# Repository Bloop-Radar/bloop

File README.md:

# Bloop Radar Platform

**Note: Hardware is still under heavy development. Please use at your own risk.**

## What is Bloop?
Bloop is an open-source 24 GHz radar platform aimed to be an easy way for hobbyists, students, and engineers to learn and experiment with radar. 

The goal for this project is not to make an application-specific radar but instead create a flexible platform to learn more about doppler and FMCW radar principles. In order to accomplish this the hardware must be low cost, modular, and allow people to develop their own applications easily. 

Currently, the software solution for Bloop is still unknown as the hardware is still being developed. The plan is to use the ECP5 as the FPGA for this platform and open-source FPGA toolchains available such as [Yosys](https://github.com/YosysHQ/yosys) and [nextpnr](https://github.com/YosysHQ/nextpnr).

## Hardware
The hardware will consist of three modules: an **antenna module** (work in progress), **RF module** ([BGT24 Module](#bgt24-module---rev-a)), and **digital module** (work in progress).

### Planned Hardware Specifications 
* 24 GHz Transceiver MMIC ([BGT24MTR12](https://www.infineon.com/cms/en/product/sensor/radar-image-sensors/radar-sensors/radar-sensors-for-consumer-and-iot/bgt24mtr12/?redirId=117670))
  * 1 TX SMP Connector
  * 2 RX SMP Connectors
* PLL with chirp generation ([LMX2491](http://www.ti.com/product/LMX2491))
* 4 Channel ADC ([ADAR7251](https://www.analog.com/en/products/adar7251.html#))
* ECP5 FPGA
* USB
* ... and more TBD

### BGT24 Module - Rev A

The BGT24 Module is the RF module for the Bloop radar platform, which provides differential I/Q data for RX1 and RX2 along with SPI and modulation control for the LMX2491 PLL and BGT24MTR12 RF transceiver. 

This module will continue to evolve as we test with the SPI Control prototyping hardware and develop some PCB antennas to test with.  

## Prototyping Hardware
Hardware found under `hardware/prototypes` is solely used to develop/evaluate the function of the RF section, BGT24 module, and the ADAR7251 ADC.

### SPI Control - Rev A
Work In Progress under branch `spi_control`  

The SPI Control hardware will include a USB-SPI controller for evaluating the BGT24 Module and ADC. The board will also include an external connector to interface with FPGA development boards.

### RF Front-End - Rev A
The RF Front-End is a panel of various RF microstrip structures to be evaluated for the RF section.

## License
Bloop hardware is distributed under the [Creative Commons Attribution Share Alike 4.0 International](LICENSE.txt)

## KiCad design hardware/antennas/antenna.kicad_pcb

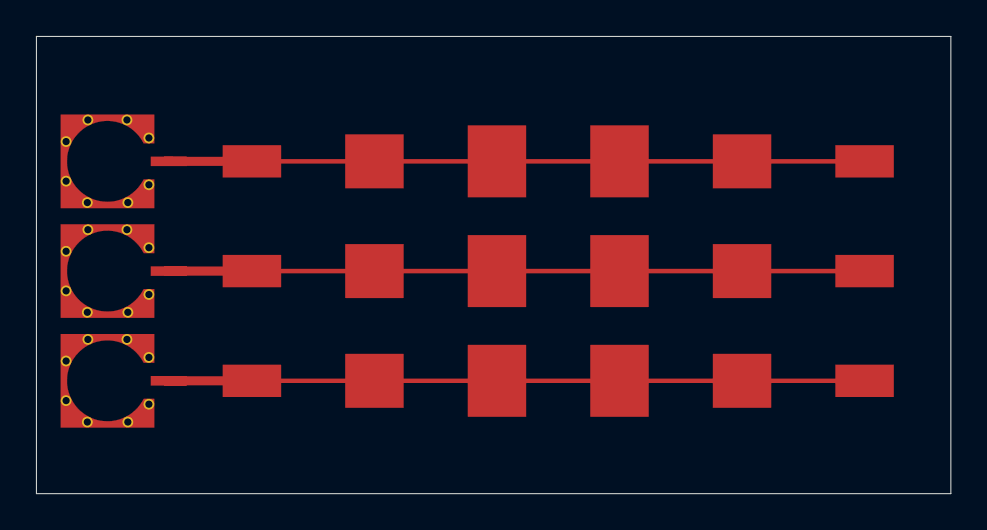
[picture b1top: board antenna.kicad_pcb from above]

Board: 2 copper layers, 50.8 x 25.4 mm, 6 parts (0 on the bottom side), 4 nets, no tracks yet.

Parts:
AE1, AE2, AE3: Antenna; SFPatch_v1
J1, J2, J3: SMP; 85305-0232

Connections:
GNDRF: J1.2, J2.2, J3.2
unnamed: AE1.1, J1.1
unnamed: AE2.1, J2.1
unnamed: AE3.1, J3.1

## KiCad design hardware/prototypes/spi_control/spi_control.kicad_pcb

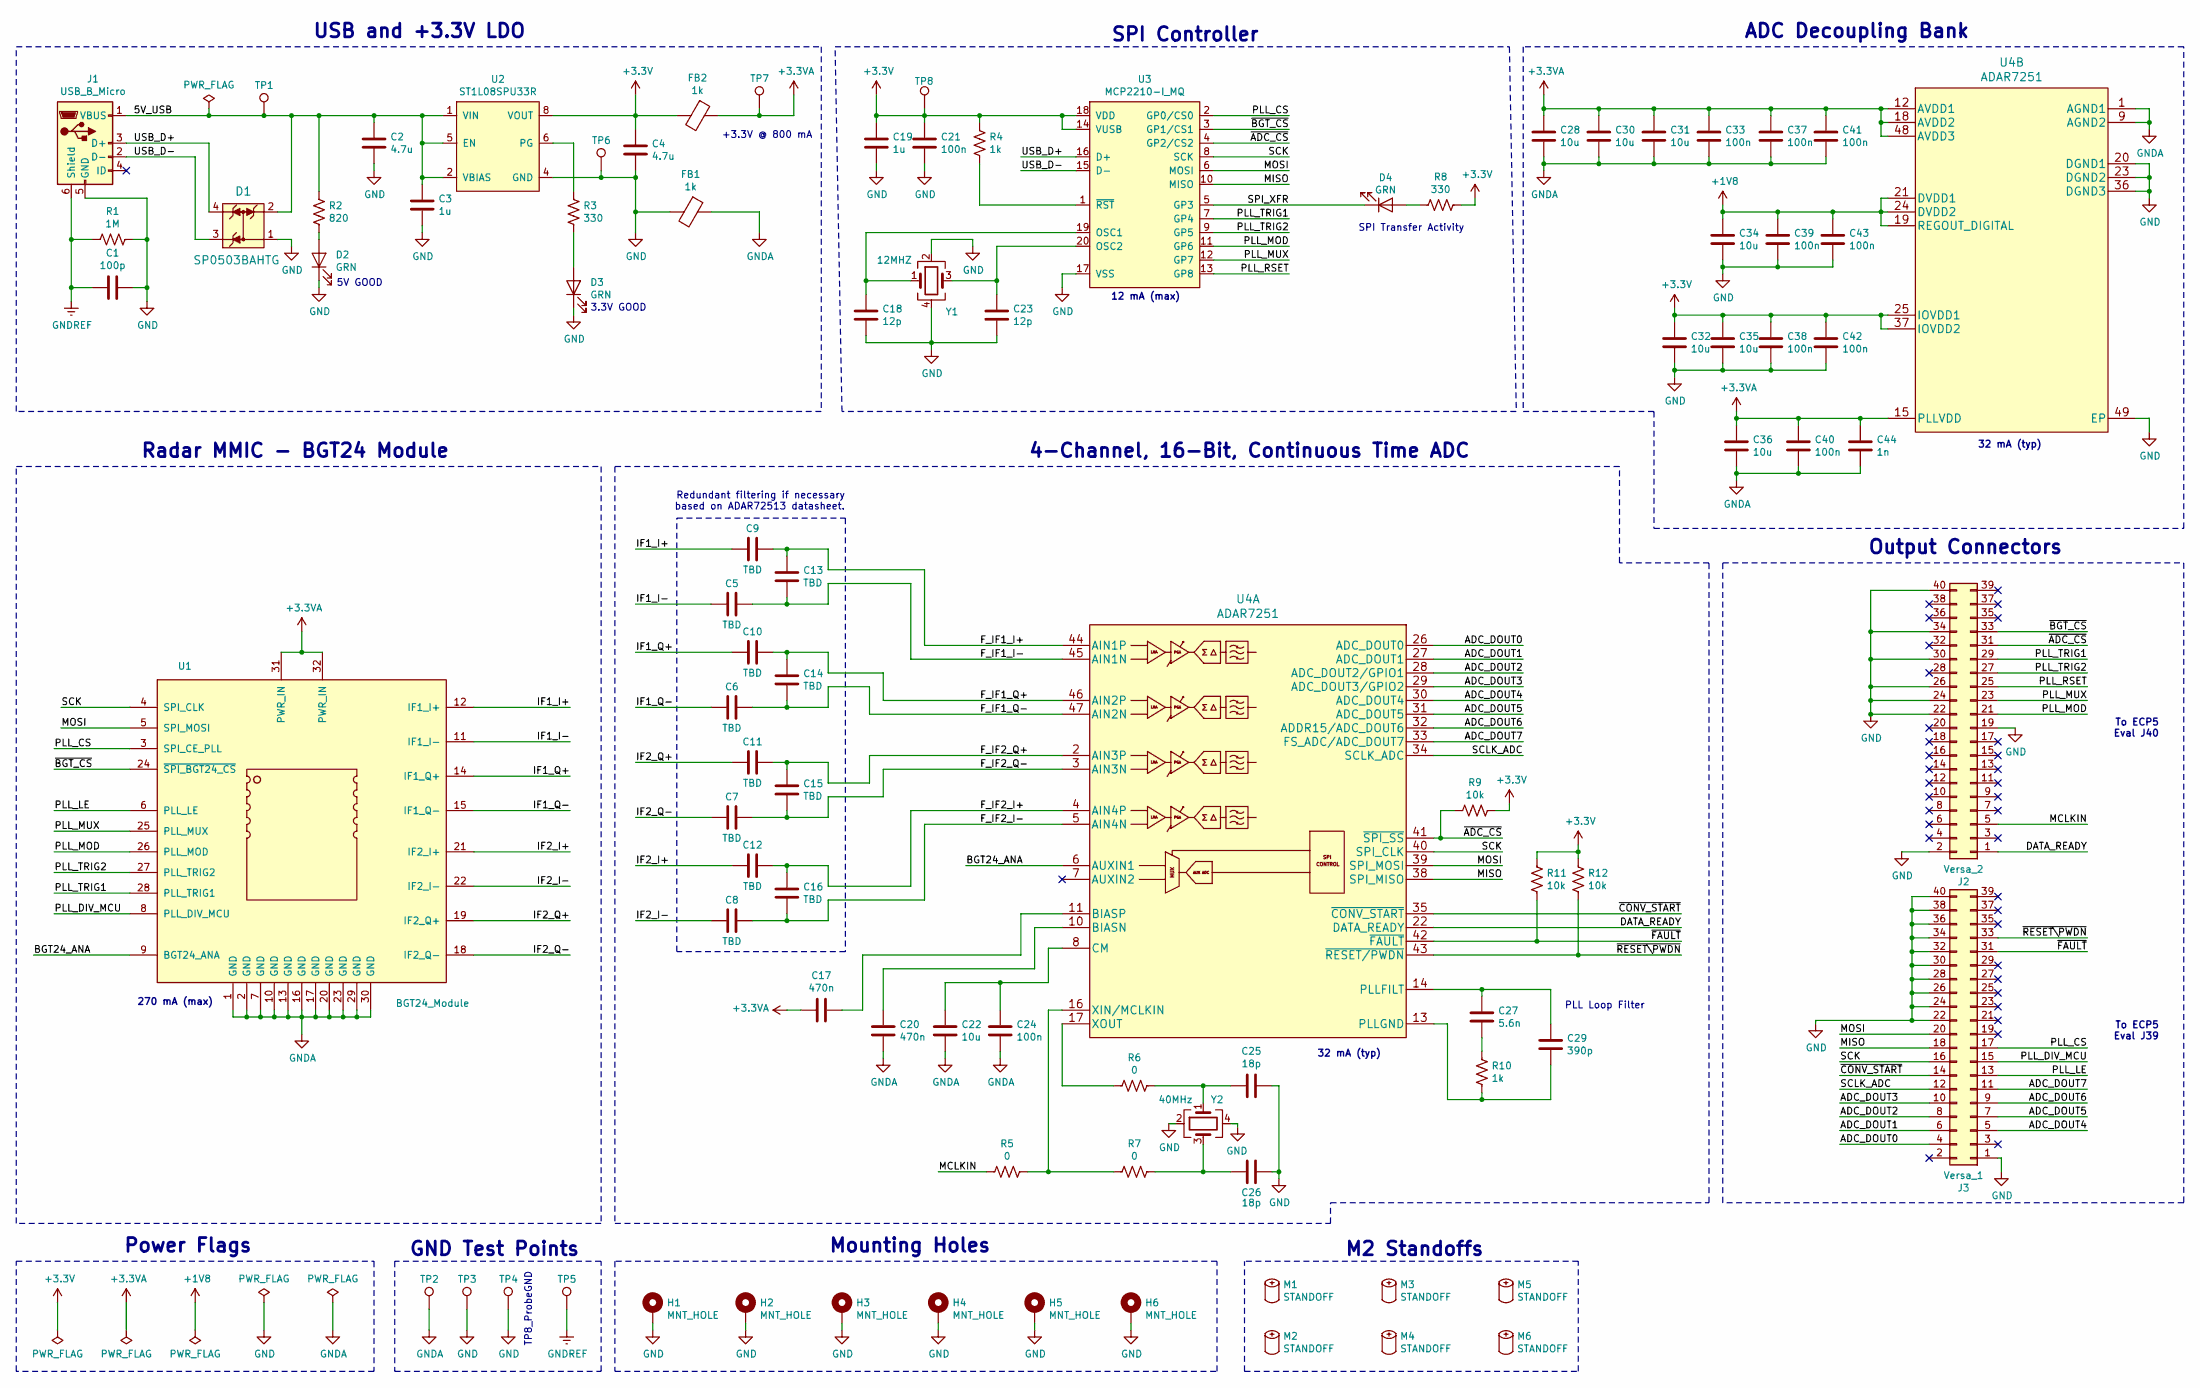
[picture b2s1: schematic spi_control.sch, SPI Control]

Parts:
C1: 100p; C_0402_1005Metric; MPN GCM1555C1H101JA16D; Digi-Key_PN 490-10669-1-ND
C2, C4: 4.7u; C_0402_1005Metric; MPN GRM155R60J475ME47D; Digi-Key_PN 490-5915-1-ND
C3, C19: 1u; C_0402_1005Metric; MPN CL05A105MQ5NNNC; Digi-Key_PN 1276-1235-1-ND
C5, C6, C7, C8, C9, C10, C11, C12, C13, C14, C15, C16: TBD; C_0402_1005Metric
C17, C20: 470n; C_0402_1005Metric; MPN CL05A474KQ5NNNC; Digi-Key_PN 1276-1479-1-ND
C18, C23: 12p; C_0402_1005Metric; MPN C0402C120J5GACTU; Digi-Key_PN 399-1013-1-ND
C21, C24, C33, C37, C38, C39, C40, C41, C42, C43: 100n; C_0402_1005Metric; MPN CL05A104KQ5NNNC; Digi-Key_PN 1276-1442-1-ND
C22, C28, C30, C31, C32, C34, C35, C36: 10u; C_0402_1005Metric; MPN GRM155C80J106ME11D; Digi-Key_PN 490-13233-1-ND
C25, C26: 18p; C_0402_1005Metric; MPN 04025A180JAT2A; Digi-Key_PN 478-1073-1-ND
C27: 5.6n; C_0402_1005Metric; MPN CL05B562KA5NNNC; Digi-Key_PN 1276-1578-1-ND
C29: 390p; C_0402_1005Metric; MPN CL05B391KB5NNNC; Digi-Key_PN 1276-1560-1-ND
C44: 1n; C_0402_1005Metric; MPN C0402C102K5RACTU; Digi-Key_PN 399-1032-1-ND
D1: SP0503BAHTG; SOT-143; MPN SP0503BAHTG; Digi-Key_PN F2715CT-ND
D2, D3, D4: GRN; LED_0402_1005Metric; MPN SML-P13PTT86R; Digi-Key_PN 846-1197-1-ND
FB1, FB2: 1k; L_0603_1608Metric; MPN 742792662; Digi-Key_PN 732-4670-1-ND
H1, H2, H3, H4, H5, H6: MNT_HOLE; MountingHole_2.2mm_M2_Pad_Via
J1: USB_B_Micro; USB_Micro-B_Molex_47346-0001; MPN 10118193-0001LF; Digi-Key_PN 609-4616-1-ND
J2: Versa_2; PinSocket_2x20_P2.54mm_Vertical_SMD; MPN NPTC202KFMS-RC; Digi-Key_PN S5690-ND
J3: Versa_1; PinSocket_2x20_P2.54mm_Vertical_SMD; MPN NPTC202KFMS-RC; Digi-Key_PN S5690-ND
M1, M2, M3, M4, M5, M6: STANDOFF; MPN 970120244; Digi-Key_PN 732-12852-ND
R1: 1M; R_0402_1005Metric; MPN RC0402FR-071ML; Digi-Key_PN 311-1.00MLRCT-ND
R2: 820; R_0402_1005Metric; MPN RC0402JR-07820RL; Digi-Key_PN 311-820JRCT-ND
R3, R8: 330; R_0402_1005Metric; MPN RC0402FR-07330RL; Digi-Key_PN 311-330LRCT-ND
R4, R10: 1k; R_0402_1005Metric; MPN RC0402FR-071KL; Digi-Key_PN 311-1.00KLRCT-ND
R5, R6, R7: 0; R_0402_1005Metric; MPN RC0402JR-070RL; Digi-Key_PN 311-0.0JRCT-ND
R9, R11, R12: 10k; R_0402_1005Metric; MPN RC0402FR-0710KL; Digi-Key_PN 311-10.0KLRCT-ND
TP1, TP2, TP3, TP5, TP6, TP7, TP8: TestPoint; TestPoint_Pad_D1.0mm
TP4: TestPoint; TestPoint_Keystone_5019_Minature; MPN 5019; Digi-Key_PN 36-5019CT-ND
U1: BGT24_Module
U2: ST1L08SPU33R; DFN-8-1EP_2x3mm_P0.5mm_EP0.61x2.2mm; MPN ST1L08SPU33R; Digi-Key_PN 497-15508-1-ND
U3: MCP2210-I_MQ; QFN-20-1EP_5x5mm_P0.65mm_EP3.35x3.35mm; MPN MCP2210-I/MQ; Digi-Key_PN MCP2210-I/MQ-ND
U4: ADAR7251; LFCSP-48-1EP_7x7mm_P0.5mm_EP4.1x4.1mm; MPN ADAR7251WBCSZ; Digi-Key_PN ADAR7251WBCSZ-ND
Y1: 12MHZ; Crystal_SMD_Abracon_ABM8G-4Pin_3.2x2.5mm; MPN ECS-120-12-33-AGN-TR; Digi-Key_PN XC2611CT-ND
Y2: 40MHz; Crystal_SMD_Abracon_ABM8G-4Pin_3.2x2.5mm; MPN ECS-400-18-33-JGN-TR; Digi-Key_PN XC2717CT-ND

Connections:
+1V8: C34.1, C39.1, C43.1, U4.19 (REGOUT_DIGITAL), U4.21 (DVDD1), U4.24 (DVDD2)
+3.3VA: C17.2, C28.1, C30.1, C31.1, C33.1, C36.1, C37.1, C40.1, C41.1, C44.1, FB2.1, TP7.1, U1.31 (PWR_IN), U1.32 (PWR_IN), U4.12 (AVDD1), U4.15 (PLLVDD), U4.18 (AVDD2), U4.48 (AVDD3)
+3V3: C4.1, C19.1, C21.1, C32.1, C35.1, C38.1, C42.1, FB2.2, R4.2, R8.1, R9.1, R11.1, R12.1, TP8.1, U2.8 (VOUT), U3.14 (VUSB), U3.18 (VDD), U4.25 (IOVDD1), U4.37 (IOVDD2)
/5V_USB: C2.1, C3.1, D1.2, J1.1 (VBUS), R2.2, TP1.1, U2.1 (VIN), U2.2 (VBIAS), U2.5 (EN)
/ADC_DOUT0: J3.4, U4.26 (ADC_DOUT0)
/ADC_DOUT1: J3.6, U4.27 (ADC_DOUT1)
/ADC_DOUT2: J3.8, U4.28 (ADC_DOUT2/GPIO1)
/ADC_DOUT3: J3.10, U4.29 (ADC_DOUT3/GPIO2)
/ADC_DOUT4: J3.5, U4.30 (ADC_DOUT4)
/ADC_DOUT5: J3.7, U4.31 (ADC_DOUT5)
/ADC_DOUT6: J3.9, U4.32 (ADDR15/ADC_DOUT6)
/ADC_DOUT7: J3.11, U4.33 (FS_ADC/ADC_DOUT7)
/BGT24_ANA: U1.9 (BGT24_ANA), U4.6 (AUXIN1)
/DATA_READY: J2.1, U4.22 (DATA_READY)
/F_IF1_I+: C9.2, C13.2, U4.44 (AIN1P)
/F_IF1_I-: C5.2, C13.1, U4.45 (AIN1N)
/F_IF1_Q+: C10.2, C14.2, U4.46 (AIN2P)
/F_IF1_Q-: C6.2, C14.1, U4.47 (AIN2N)
/F_IF2_I+: C12.2, C16.2, U4.4 (AIN4P)
/F_IF2_I-: C8.2, C16.1, U4.5 (AIN4N)
/F_IF2_Q+: C11.2, C15.2, U4.2 (AIN3P)
/F_IF2_Q-: C7.2, C15.1, U4.3 (AIN3N)
/IF1_I+: C9.1, U1.12 (IF1_I+)
/IF1_I-: C5.1, U1.11 (IF1_I-)
/IF1_Q+: C10.1, U1.14 (IF1_Q+)
/IF1_Q-: C6.1, U1.15 (IF1_Q-)
/IF2_I+: C12.1, U1.21 (IF2_I+)
/IF2_I-: C8.1, U1.22 (IF2_I-)
/IF2_Q+: C11.1, U1.19 (IF2_Q+)
/IF2_Q-: C7.1, U1.18 (IF2_Q-)
/MCLKIN: J2.5, R5.2
/MISO: J3.18, U3.10 (MISO), U4.38 (SPI_MISO)
/MOSI: J3.20, U1.5 (SPI_MOSI), U3.6 (MOSI), U4.39 (SPI_MOSI)
/PLL_CS: J3.17, U1.3 (SPI_CE_PLL), U3.2 (GP0/CS0)
/PLL_DIV_MCU: J3.15, U1.8 (PLL_DIV_MCU)
/PLL_LE: J3.13, U1.6 (PLL_LE)
/PLL_MOD: J2.21, U1.26 (PLL_MOD), U3.11 (GP6)
/PLL_MUX: J2.23, U1.25 (PLL_MUX), U3.12 (GP7)
/PLL_RSET: J2.25, U3.13 (GP8)
/PLL_TRIG1: J2.29, U1.28 (PLL_TRIG1), U3.7 (GP4)
/PLL_TRIG2: J2.27, U1.27 (PLL_TRIG2), U3.9 (GP5)
/SCK: J3.16, U1.4 (SPI_CLK), U3.8 (SCK), U4.40 (SPI_CLK)
/SCLK_ADC: J3.12, U4.34 (SCLK_ADC)
/SPI_XFR: D4.1 (K), U3.5 (GP3)
/USB_D+: D1.4, J1.3 (D+), U3.16 (D+)
/USB_D-: D1.3, J1.2 (D-), U3.15 (D-)
/~ADC_CS: J2.31, R9.2, U3.4 (GP2/CS2), U4.41 (~SPI_SS)
/~BGT_CS: J2.33, U1.24 (~SPI_BGT24_CS), U3.3 (GP1/CS1)
/~CONV_START: J3.14, U4.35 (~CONV_START)
/~FAULT: J3.31, R11.2, U4.42 (~FAULT)
/~RESET\PWDN: J3.33, R12.2, U4.43 (~RESET/PWDN)
GND: C1.2, C2.2, C3.2, C4.2, C18.1, C19.2, C21.2, C23.1, C25.1, C26.1, C32.2, C34.2, C35.2, C38.2, C39.2, C42.2, C43.2, D1.1, D2.1 (K), D3.1 (K), FB1.2, H1.1, H2.1, H3.1, H4.1, H5.1, H6.1, J1.5 (GND), J2.2, J2.19, J2.22, J2.24, J2.26, J2.30, J2.34, J2.40, J3.1, J3.22, J3.24, J3.26, J3.28, J3.30, J3.32, J3.34, J3.36, J3.38, J3.40, R1.2, TP3.1, TP4.1, TP6.1, U2.4 (GND), U3.17 (VSS), U4.20 (DGND1), U4.23 (DGND2), U4.36 (DGND3), U4.49 (EP), Y1.2, Y1.4, Y2.2, Y2.4
GNDA: C20.2, C22.2, C24.2, C28.2, C30.2, C31.2, C33.2, C36.2, C37.2, C40.2, C41.2, C44.2, FB1.1, TP2.1, U1.1 (GND), U1.2 (GND), U1.7 (GND), U1.10 (GND), U1.13 (GND), U1.16 (GND), U1.17 (GND), U1.20 (GND), U1.23 (GND), U1.29 (GND), U1.30 (GND), U4.1 (AGND1), U4.9 (AGND2)
GNDREF: C1.1, J1.6 (Shield), R1.1, TP5.1
unnamed: C17.1, U4.11 (BIASP)
unnamed: C18.2, U3.19 (OSC1), Y1.1
unnamed: C20.1, U4.10 (BIASN)
unnamed: C22.1, C24.1, U4.8 (CM)
unnamed: C23.2, U3.20 (OSC2), Y1.3
unnamed: C25.2, R6.1, Y2.1
unnamed: C26.2, R7.1, Y2.3
unnamed: C27.1, C29.1, U4.14 (PLLFILT)
unnamed: C27.2, R10.1
unnamed: C29.2, R10.2, U4.13 (PLLGND)
unnamed: D2.2 (A), R2.1
unnamed: D3.2 (A), R3.1
unnamed: D4.2 (A), R8.2
unnamed: R3.2, U2.6 (PG)
unnamed: R4.1, U3.1 (~RST)
unnamed: R5.1, R7.2, U4.16 (XIN/MCLKIN)
unnamed: R6.2, U4.17 (XOUT)

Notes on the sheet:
5V GOOD
3.3V GOOD
SPI Controller
USB and +3.3V LDO
PLL Loop Filter
Power Flags
12 mA (max)
ADC Decoupling Bank
Output Connectors
SPI Transfer Activity
4-Channel, 16-Bit, Continuous Time ADC
GND Test Points
Redundant filtering if necessary based on ADAR72513 datasheet.
Radar MMIC - BGT24 Module
TP8_ProbeGND
Mounting Holes
32 mA (typ)
M2 Standoffs
270 mA (max)
+3.3V @ 800 mA
To ECP5 Eval J40
To ECP5 Eval J39

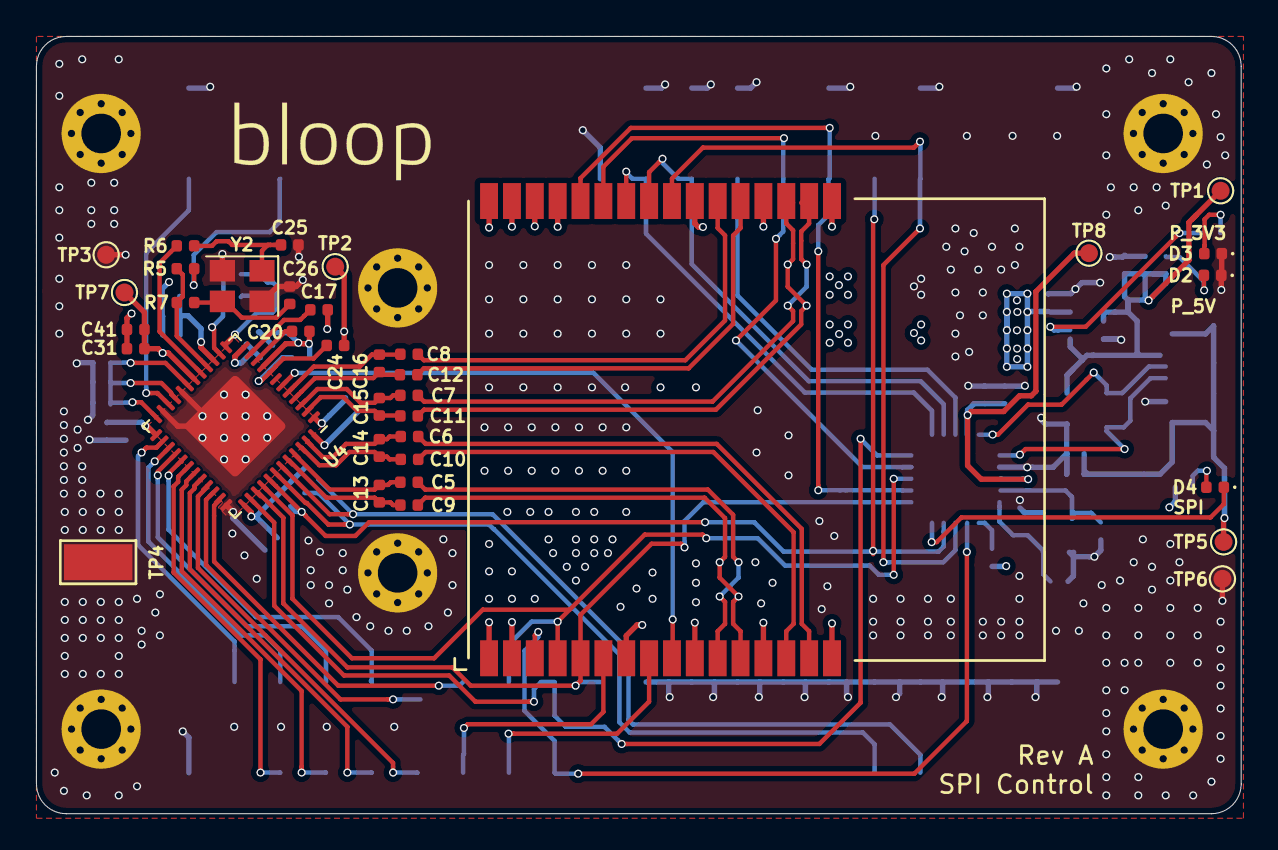
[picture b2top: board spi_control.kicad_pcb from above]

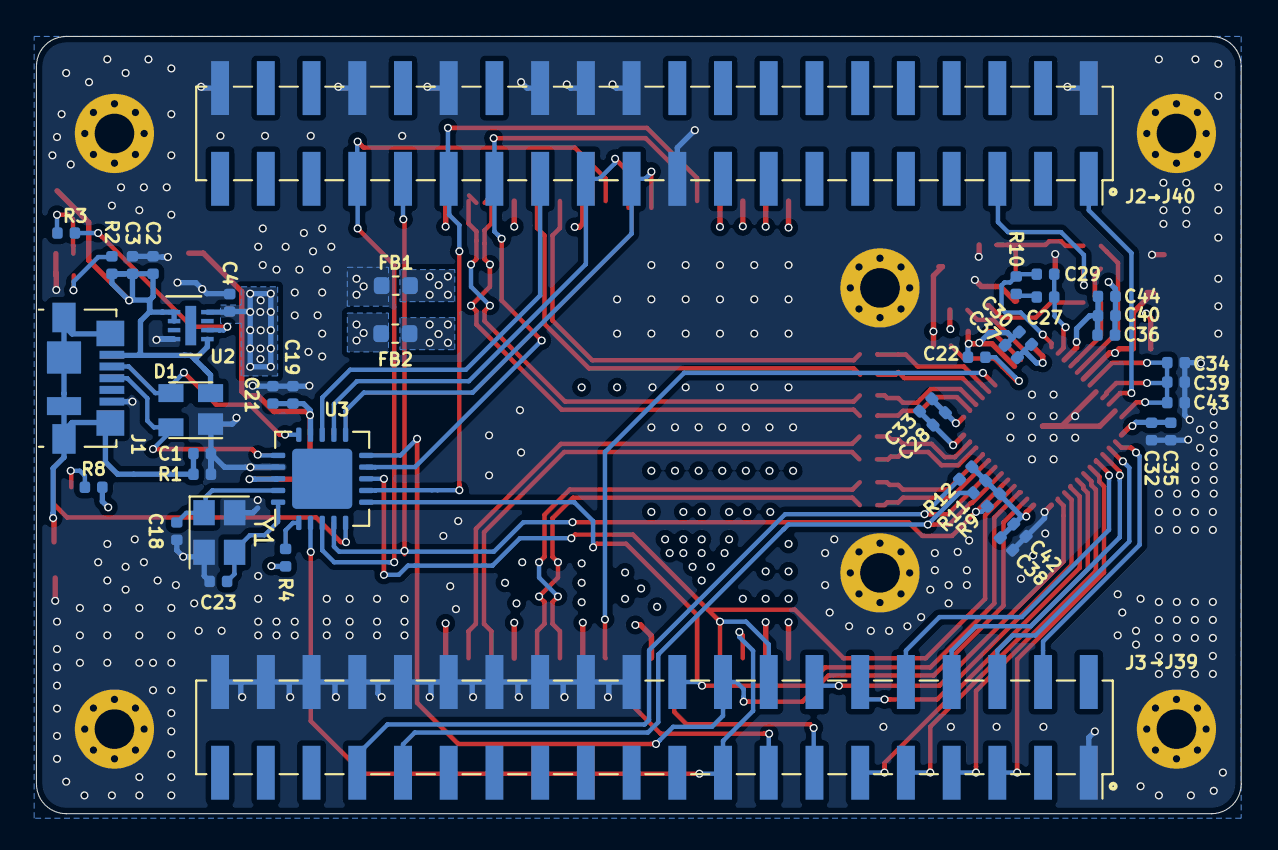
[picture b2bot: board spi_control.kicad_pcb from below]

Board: 4 copper layers, 66.9 x 43.2 mm, 85 parts (43 on the bottom side), 71 nets.

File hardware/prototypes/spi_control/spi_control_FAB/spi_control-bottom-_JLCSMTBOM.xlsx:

Comment | Designator | Footprint | Description
100n | C21, C33, C37, C38, C39, C40, C42, C43 | C_0402_1005Metric | CAP CER 0.1UF 6.3V X5R 0402
1n | C44 | C_0402_1005Metric | CAP CER 1000PF 50V X7R 0402
100p | C1 | C_0402_1005Metric | CAP CER 100PF 50V C0G/NP0 0402
10u | C22, C28, C30, C32, C34, C35, C36 | C_0402_1005Metric | CAP CER 10UF 6.3V X6S 0402
12p | C18, C23 | C_0402_1005Metric | CAP CER 12PF 50V C0G/NP0 0402
1u | C3, C19 | C_0402_1005Metric | CAP CER 1UF 6.3V X5R 0402
390p | C29 | C_0402_1005Metric | CAP CER 390PF 50V X7R 0402
4.7u | C2, C4 | C_0402_1005Metric | CAP CER 4.7UF 6.3V X5R 0402
5.6n | C27 | C_0402_1005Metric | CAP CER 5600PF 25V X7R 0402
10k | R9, R11, R12 | R_0402_1005Metric | RES SMD 10K OHM 1% 1/16W 0402
1k | R4, R10 | R_0402_1005Metric | RES SMD 1K OHM 1% 1/16W 0402
1M | R1 | R_0402_1005Metric | RES SMD 1M OHM 1% 1/16W 0402
330 | R3, R8 | R_0402_1005Metric | RES SMD 330 OHM 1% 1/16W 0402
820 | R2 | R_0402_1005Metric | RES SMD 820 OHM 5% 1/16W 0402
SP0503BAHTG | D1 | SOT-143 | TVS DIODE 5.5V 8.5V SOT143-4
MCP2210-I_MQ | U3 | QFN-20-1EP_5x5mm_P0.65mm_EP3.35x3.35mm | IC CONVERTER USB-SPI 20-QFN
ST1L08SPU33R | U2 | DFN-8-1EP_2x3mm_P0.5mm_EP0.61x2.2mm | IC REG LINEAR 3.3V 800MA 8DFN
12MHZ | Y1 | Crystal_SMD_Abracon_ABM8G-4Pin_3.2x2.5mm | CRYSTAL 12MHZ 12PF SMD
1k | FB1, FB2 | L_0603_1608Metric | FERRITE BEAD 1 KOHM 0603 1LN
Versa_2 | J2 | PinSocket_2x20_P2.54mm_Vertical_SMD | CONN HDR 40POS 0.1 TIN SMD
Versa_1 | J3 | PinSocket_2x20_P2.54mm_Vertical_SMD | CONN HDR 40POS 0.1 TIN SMD
USB_B_Micro | J1 | USB_Micro-B_Molex_47346-0001 | CONN RCPT USB2.0 MICRO B SMD R/A

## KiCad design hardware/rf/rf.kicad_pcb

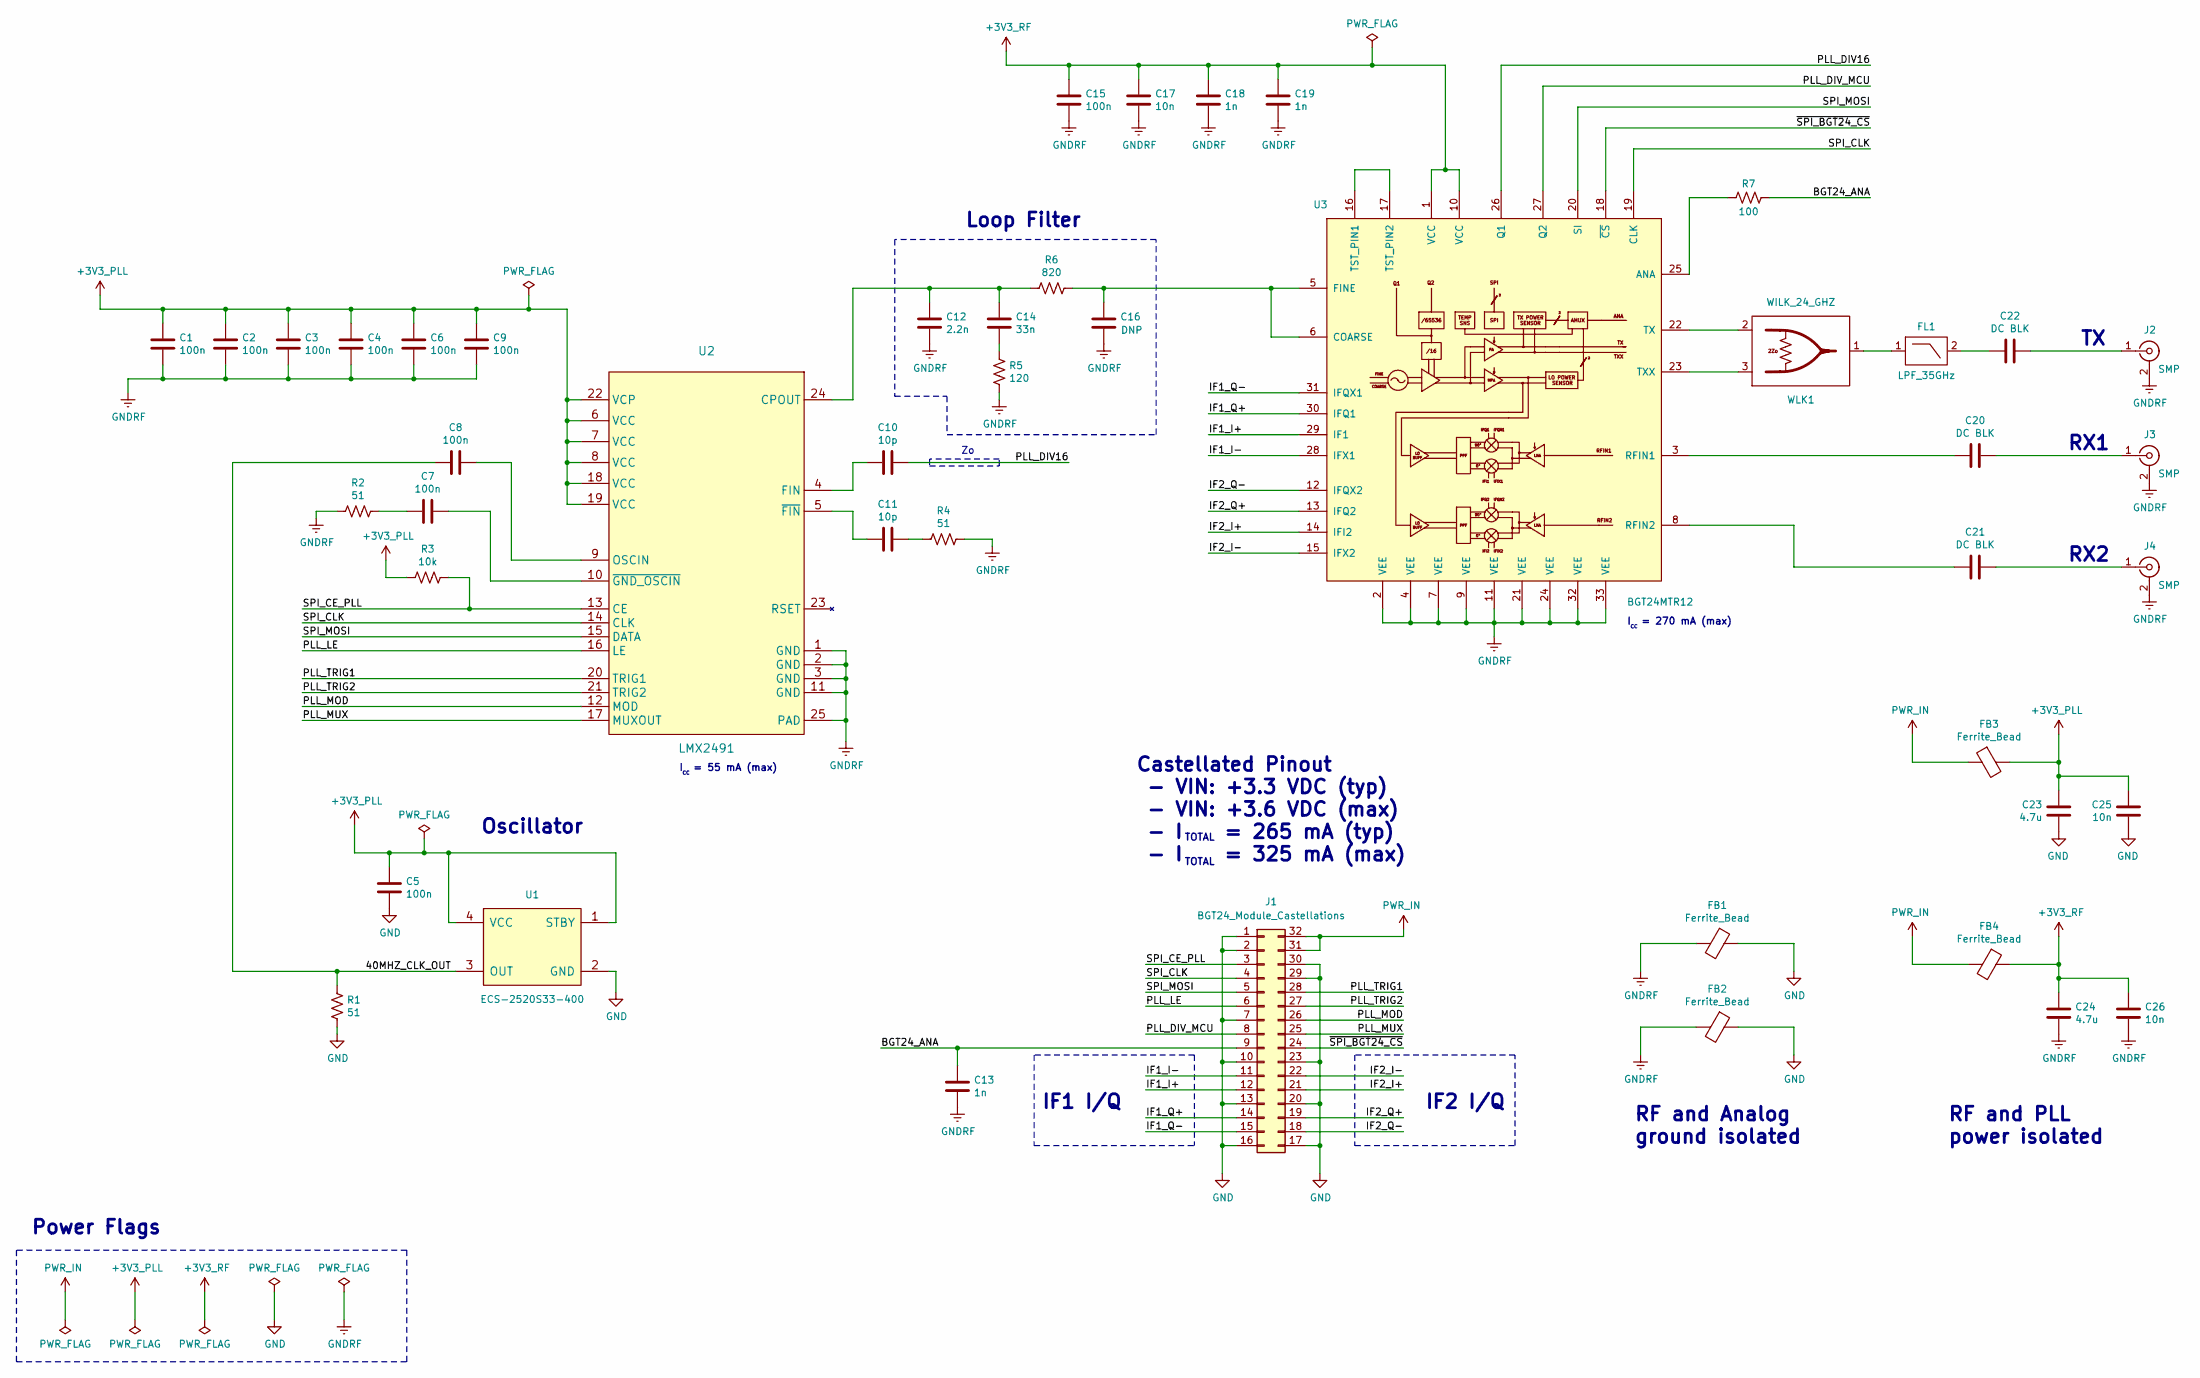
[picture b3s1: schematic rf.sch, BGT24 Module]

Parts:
C1, C2, C3, C4, C5, C6, C7, C8, C9, C15: 100n; C_0201_0603Metric; MPN GRM033R6YA104KE14D
C10, C11: 10p; C_0402_1005Metric; MPN GCM1555C1H100GA16D
C12: 2.2n; C_0201_0603Metric; MPN GRM033R61C223KE84D
C13, C18, C19: 1n; C_0201_0603Metric; MPN GRM033R71H102KA12D
C14: 33n; C_0201_0603Metric; MPN GRM033R61C333KE84D
C16: C_0201_0603Metric
C17, C25, C26: 10n; C_0201_0603Metric; MPN GRM033R71E103KE14D
C20, C21, C22: DC BLK; DC_Block
C23, C24: 4.7u; C_0603_1608Metric; MPN GRM188R61E475KE11D
FB1, FB2, FB3, FB4: Ferrite_Bead; L_0402_1005Metric; MPN MPZ1005S121CT000
FL1: LPF_35GHz; 35GHz_LPF
J1: BGT24_Module_Castellations
J2, J3, J4: SMP; 85305-0232; MPN 0853050232
R1, R2, R4: 51; R_0201_0603Metric; MPN ERJ-1GNF51R0C
R3: 10k; R_0201_0603Metric; MPN ERJ-1GNF1002C
R5: 120; R_0201_0603Metric; MPN ERJ-1GNJ121C
R6: 820; R_0201_0603Metric; MPN ERJ-1GNF8200C
R7: 100; R_0201_0603Metric; MPN ERJ-1GNF1000C
U1: ECS-2520S33-400; Crystal_SMD_2520-4Pin_2.5x2.0mm; MPN ECS-2520S33-400-FN-TR
U2: LMX2491; VQFN-24-1EP_4x4mm_P0.5mm_EP2.45x2.45mm; MPN LMX2491RTWR
U3: BGT24MTR12; MPN BGT24MTR12E6327XUMA1
WLK1: WILK_24_GHZ; Wilk_AWR_Mod

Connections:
+3V3_PLL: C1.1, C2.1, C3.1, C4.1, C5.1, C6.1, C9.1, C23.1, C25.1, FB3.2, R3.2, U1.1 (STBY), U1.4 (VCC), U2.6 (VCC), U2.7 (VCC), U2.8 (VCC), U2.18 (VCC), U2.19 (VCC), U2.22 (VCP)
+3V3_RF: C15.1, C17.1, C18.1, C19.1, C24.1, C26.1, FB4.1, U3.1 (VCC), U3.10 (VCC)
/40MHZ_CLK_OUT: C8.1, R1.1, U1.3 (OUT)
/BGT24_ANA: C13.1, J1.9, R7.1
/IF1_I+: J1.12, U3.29 (IF1)
/IF1_I-: J1.11, U3.28 (IFX1)
/IF1_Q+: J1.14, U3.30 (IFQ1)
/IF1_Q-: J1.15, U3.31 (IFQX1)
/IF2_I+: J1.21, U3.14 (IFI2)
/IF2_I-: J1.22, U3.15 (IFX2)
/IF2_Q+: J1.19, U3.13 (IFQ2)
/IF2_Q-: J1.18, U3.12 (IFQX2)
/PLL_DIV16: C10.1, U3.26 (Q1)
/PLL_DIV_MCU: J1.8, U3.27 (Q2)
/PLL_LE: J1.6, U2.16 (LE)
/PLL_MOD: J1.26, U2.12 (MOD)
/PLL_MUX: J1.25, U2.17 (MUXOUT)
/PLL_TRIG1: J1.28, U2.20 (TRIG1)
/PLL_TRIG2: J1.27, U2.21 (TRIG2)
/SPI_CE_PLL: J1.3, R3.1, U2.13 (CE)
/SPI_CLK: J1.4, U2.14 (CLK), U3.19 (CLK)
/SPI_MOSI: J1.5, U2.15 (DATA), U3.20 (SI)
/~SPI_BGT24_CS: J1.24, U3.18 (~CS)
GND: C5.2, C23.2, C25.2, FB1.1, FB2.1, J1.1, J1.2, J1.7, J1.10, J1.13, J1.16, J1.17, J1.20, J1.23, J1.29, J1.30, R1.2, U1.2 (GND)
GNDRF: C1.2, C2.2, C3.2, C4.2, C6.2, C9.2, C12.2, C13.2, C15.2, C16.2, C17.2, C18.2, C19.2, C24.2, C26.2, FB1.2, FB2.2, J2.2 (Ext), J3.2 (Ext), J4.2 (Ext), R2.2, R4.1, R5.2, U2.1 (GND), U2.2 (GND), U2.3 (GND), U2.11 (GND), U2.25 (PAD), U3.2 (VEE), U3.4 (VEE), U3.7 (VEE), U3.9 (VEE), U3.11 (VEE), U3.21 (VEE), U3.24 (VEE), U3.32 (VEE), U3.33 (VEE)
unnamed: C7.1, R2.1
unnamed: C7.2, U2.10 (~GND_OSCIN)
unnamed: C8.2, U2.9 (OSCIN)
unnamed: C10.2, U2.4 (FIN)
unnamed: C11.1, R4.2
unnamed: C11.2, U2.5 (~FIN)
unnamed: C12.1, C14.1, R6.2, U2.24 (CPOUT)
unnamed: C14.2, R5.1
unnamed: C16.1, R6.1, U3.5 (FINE), U3.6 (COARSE)
unnamed: C20.1, J3.1 (In)
unnamed: C20.2, U3.3 (RFIN1)
unnamed: C21.1, J4.1 (In)
unnamed: C21.2, U3.8 (RFIN2)
unnamed: C22.1, J2.1 (In)
unnamed: C22.2, FL1.2 (OUT)
unnamed: FL1.1 (IN), WLK1.1
unnamed: R7.2, U3.25 (ANA)
unnamed: U3.16 (TST_PIN1), U3.17 (TST_PIN2)
unnamed: U3.22 (TX), WLK1.2
unnamed: U3.23 (TXX), WLK1.3
PWR_IN: FB3.1, FB4.2, J1.31, J1.32

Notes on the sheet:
Loop Filter
Power Flags
Oscillator
I = 270 mA (max)
IF2 I/Q
RF and Analog ground isolated
Castellated Pinout - VIN: +3.3 VDC (typ) - VIN: +3.6 VDC (max) - I = 265 mA (typ) - I = 325 mA (max)
TOTAL
I = 55 mA (max)
RX1
RX2
IF1 I/Q
RF and PLL power isolated

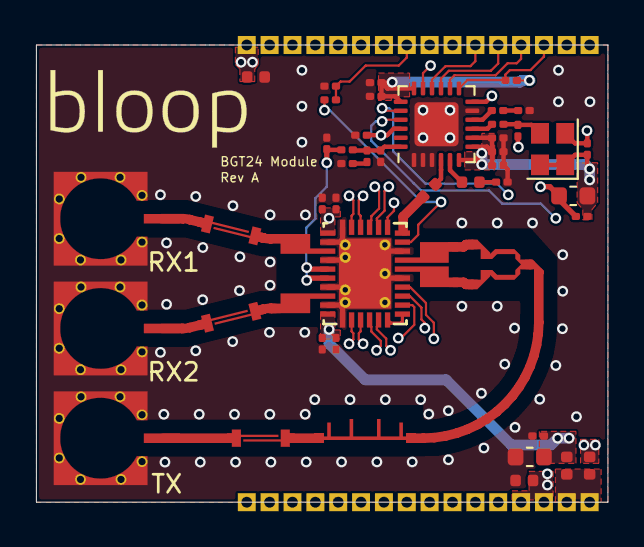
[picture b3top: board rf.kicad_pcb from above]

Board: 4 copper layers, 31.8 x 25.4 mm, 46 parts (1 on the bottom side), 46 nets.

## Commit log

2019-07-27 Initial radar pcb project framework Added 35GHz_LPF footprint
2019-07-27 Created Schematic Worksheet
2019-07-27 Added bloop schematic symbol library Added LPF_35GHz schematic symbol
2019-07-28 Make worksheet template relative-path based
2019-07-28 Added schematic hierarchial sheets
2019-07-28 Radar MMIC symbol; Pcbnew worksheet template added to bloop.kicad_pcb
2019-07-28 Add background color to radar MMIC symbol
2019-07-28 Add wilkinson symbol
2019-07-28 Added 3d SMP footprint and model
2019-07-28 Corrected 3d model path for SMP connector 0734153320
2019-07-28 Added BGT24MTR12 VQFN-32-9 footprint Updated gold material on 3d model 734153320
2019-07-28 Rearrange pins for aesthetic reasons
2019-07-28 Add rev; add titles to schematic sheets
2019-07-28 Move power sheet box
2019-07-28 Make schematic box text size larger
2019-07-28 Started PLL circuitry Added PLL device and oscillator Still need loop filter and clock filter circuits
2019-07-29 Add DC blocking capacitors; add larger resistor and capacitor symbols; implement root PN for symbols
2019-07-30 fixing MPNs
2019-08-06 Add stubs to RX portion; move blocking caps
2019-08-10 Updates to footprint library
2019-08-10 Add edge-launch SWM connector footprint and 3D model
2019-08-10 Preliminary layout
2019-08-11 Layout edits
2019-08-11 Add 100 ohm resistors to wilkinson dividers
2019-08-11 Created Wilk1.mod
2019-08-11 Updates to front end layout
2019-08-16 Remove paste layer from filters; increase mask distance on front_end board
2019-08-19 Corrected transmision line clearance
2019-08-25 Added Infineon Wilkinson
2019-08-25 Corrected Infineon Wilkinson footprint
2019-08-25 Infineon Netclass
2019-08-25 Added infineon wilkinson to layout
2019-08-25 Added Taper 8 24Ghz wilk/matched on PCB
    Added Taper 8 24Ghz wilk/matched on PCB
2019-09-14 Started rough layout for panelization of front end pcbs
2019-09-14 Removed matching stubs from front end schematic
2019-09-15 Preliminary panel for front end pcbs
2019-09-15 Updated panel tab footprint
2019-09-15 Added via stitching to front end pcbs
2019-09-15 Added bloop logo and corrections to front end layout
2019-09-15 Fixed keepouts on front end pcb layout
2019-09-17 Generated Fabrication files
2019-09-18 Incorporate template; remove temporary .sch-bak file; add bottom silk revision; remove unecessary filter half-sections; center align top silk.
2019-09-21 Added new LPF filter footprint
2019-09-22 Updated frontend layout with new LPF
2019-09-22 Include modified AWR wilkinson design; need to correct chamfers and wilkinson line lengths
2019-09-26 Front end panel edits and wilkinson length matching
2019-09-27 Add bloop logo's; correct silkscreen; change to 0402 RF footprint; add wilkinson solder mask
2019-09-28 Polish edge-launch SMA footprint
2019-09-28 Front end PCB layout edits and footprint modifications
2019-09-28 DRC check and fixes on front end pcb layout
2019-09-28 Final layout edits to front end pcb layout
2019-09-28 Fix top silk alignment; fix 0402 RF cap mask
2019-09-29 Project diretory restructuring
2019-09-30 Added new bloop logo footprint
2019-09-30 Incorporate new logo; update gerbers
2019-10-02 Changed symbol and footprint references to be relative to the project location and removed /
2019-10-06 Footprint 3d model fixes, and removed paste from microstrip filters
2019-10-11 Update bloop worksheet template
2019-10-11 Re-structure bloop folder hierarchy; create end-result pdfs of front_end; update relative paths.
2019-10-11 Initial branch structure of rf electronics board
2019-10-11 Include dcm in ignore
2019-10-13 Initial RF radar module schematic
2019-10-13 Add BGT24 radar module symbol; ignore *-cache.lib; fix digital library path
2019-10-13 Moved front_end to prototypes directory
2019-10-13 Added MCP2210-L/MQ symbol and started schematic
2019-10-13 Initial Setup
2019-10-13 Added ADAR7251 symbol and ADC schematic sections
2019-10-13 Added 3.3V LDO ST1L08SPU33R symbol. Completed power and SPI controller schematic sections
2019-10-14 Corrected ~SPI_PLL_CS to PLL_LE and changed value of U1 to display the complete MPN
2019-10-15 Setup board and layout parameters in pcbnew
2019-10-15 Added BGT24 footprint change from an incorrectly deleted commit c8d9401
2019-10-15 Directory restructuring to match master and updated symbol and footprint references
2019-10-17 Added BGT24 module castellation footprint, 3d model for 40MHz XO. Edits to schematic and pinouts based on layout of module. Initial parts placement and routing complete.
2019-10-18 Added 85305-0232 footprint for SMT SMP connector
2019-10-18 Replaced TH SMP connectors with SMT
2019-10-18 Small schematic edits
2019-10-19 Added CC-BY-SA-4.0 license
2019-10-19 Copied the SP0503BA digikey symbol to project library and replaced in schematic
2019-10-20 Add 30 mil mask; update schematic for connector orientation
2019-10-20 Add BGT24 3D model
2019-10-20 Stitched in some via-bois
2019-10-26 BGT24 module layout of PLL and via stitching
2019-10-28 BGT24 module final draft layout. Ready for review
2019-10-28 Generated schematic pdf and FAB files for review of revA BGT24 Module
2019-10-30 Layout review edits with Austin. Added BGT24 Module FAB files and started the panel for the module
2019-10-31 Updated panel with updated module layout
2019-11-01 Assigned MPNs to components and generated BOM. Small layout edits for changed part footprints
2019-11-04 Added basic 3d model for BGT24 Module footprint. Final edits to layout and panel layout. Updated FAB files for each.
2019-11-04 Updated/Added BGT24 Module schematic symbol.
2019-11-05 Modified the BGT24 Module castellations footprint to have a smaller drill diameter for a larger anular ring on the pads.
2019-11-05 Updated BGT24 Module layout and panel with new castellation footprint and adjusted some vias. Re-generated FAB outputs.
2019-11-05 SPI schema 90%
2019-11-05 Fixed AUX axis on panel layout and regenerated FAB files.
2019-11-06 Include -rescue ignore from master anddelete -rescue byproducts; bring in BGT24 module symbols/footprints from master and add relevant 3D models; beautify spi_control.sch
2019-11-07 Official BGT24 Module Rev A release. Updated README.md, BGT24 Module schematic title and added 3d render of BGT24 Module PCB. Created an 'outputs' folder for PDF schematic and renders.
2019-11-07 Update README.md
    Typo correction in README
2019-11-09 Finished connector mapping for ECP5 devboard. Versa Connector.
2019-11-09 Fixed 3D Model path for the RF castelation board. Added mounting holes for antenna secure.
2019-11-10 Aligned all holes to by symmetric and locked their position
2019-11-10 Found error in layer stackup, fixed net for top copper.
2019-11-10 finished routing power section
2019-11-10 Started routing SPI to USB. Started preliminary routing for the IQ data.
2019-11-10 finished prelim IQ routing
2019-11-10 Completed power section, completed analog power and gnd plane,fixed IQ lines to be symmetric, ADC 80% routing completed.
2019-11-10 Optimized ADC bit routing, moved nets around for J39.
2019-11-16 Finished, DRC approved, All nets routed.
2019-11-16 Fixed gnd patch on ADAR ADC footprint
2019-11-16 Added 3d model for ADAR7251 and moved footprint into bloop.pretty. Updated schematic, J39-13 swaped with J39-15. Corrected stackup text in layout to ECO1 layer from BCu.
2019-11-16 Added wonderful Silkscreen to the bottom
2019-11-16 Found mistake in header breakout, grounds were not connected. Fixed, layout and schematic.
2019-11-18 Remove Dime scale. Fill on Top layer has no net. GND Fill on Bottom layer has no net. GND Schematic: Clean up the ground connections on J40, J39, Y2, and Y1. Schematic: Remove ECP5 eval board schema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
2019-11-21 Tented the vias on the BGT24 module and the BGT24 module panel FAB files. This fixes #25
2019-12-27 Nov 17 Issues 1-22 complete.
2019-12-27 All issues EXCEPT 6,22,23 complete.
2019-12-27 Added Keystone GND probe point.
2019-12-28 Moved keystone to satisfy Leo.
2020-01-04 Generated HTML bom, Issue 6 resolved.
2020-01-04 Resolve 4, 11, 16, 18, and 25 from #24 and includes misc. improvements
2020-01-05 Resolve 9 from #24; added some vias to layout and moved a few tracks
2020-01-05 Add openEMS simulation scripts for low-pass filters and DC-block
2020-01-05 Finalize BOM, finish schematic annotations, re-generate gerbers. Close #24
2020-01-05 Finalize HTML BOM
2020-01-05 Add board dimensions in Dwgs layer
2020-01-05 Made CPL file for JLC assembly
2020-01-05 Added JLC SMT BOM for the bottom.
2020-01-07 Change to protel gerber extensions; update HTML BOM; update sch/pcb PDF outputs
2020-01-12 Created a Fab Spin folder for the recent order
2020-01-13 Removed Fab_Spin_01122020 folder
2020-02-18 First pass at a prototype series-fed patch array for experimentation purposes (tuning may be necessary)
